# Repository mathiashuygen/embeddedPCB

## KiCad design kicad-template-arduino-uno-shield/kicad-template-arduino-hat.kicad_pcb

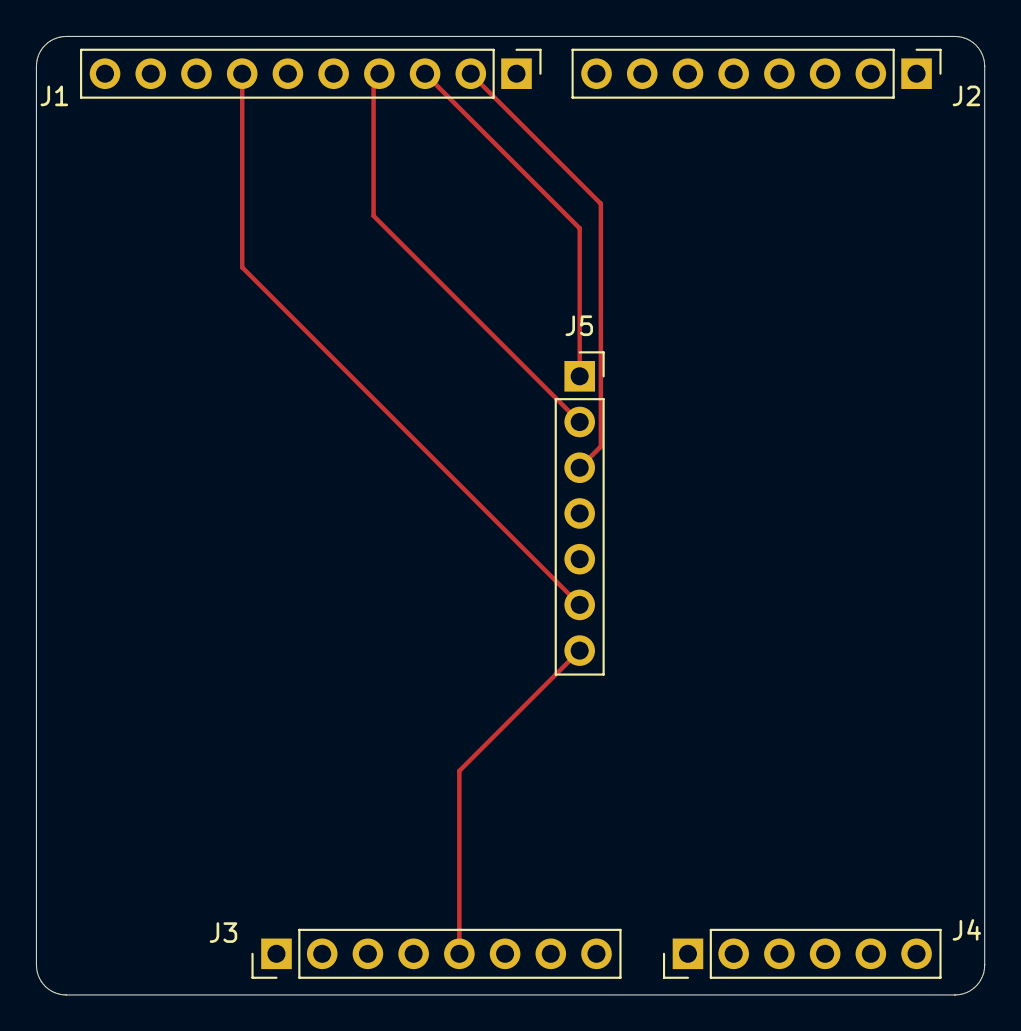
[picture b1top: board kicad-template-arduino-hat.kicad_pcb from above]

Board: 2 copper layers, 52.7 x 53.3 mm, 5 parts (0 on the bottom side), 5 nets.

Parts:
J1: Digital; PinHeader_1x10_P2.54mm_Vertical
J2: Digital; PinHeader_1x08_P2.54mm_Vertical
J3: POWER; PinHeader_1x08_P2.54mm_Vertical
J4: Analog IN; PinHeader_1x06_P2.54mm_Vertical
J5: AMP; PinSocket_1x07_P2.54mm_Vertical

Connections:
/arduino-uno-connectors/5V: J3.5, J3.8, J5.7
/arduino-uno-connectors/GND: J1.7, J3.6, J3.7, J5.6
/arduino-uno-connectors/I2S_BCLK: J1.4, J5.2
/arduino-uno-connectors/I2S_DIN: J1.2, J5.3
/arduino-uno-connectors/I2S_LRC: J1.3, J5.1

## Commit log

2026-04-04 pcb design
2026-04-18 added camera capture and audio playback
